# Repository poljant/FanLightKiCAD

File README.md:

# FanLightKiCAD
PCB FanLight
Płyta PCB do programu FanLight.
https://github.com/poljant/FanLight.git
W katalogu /GERBER/ pliki do wykonania PCB np. przez JLCPCB.

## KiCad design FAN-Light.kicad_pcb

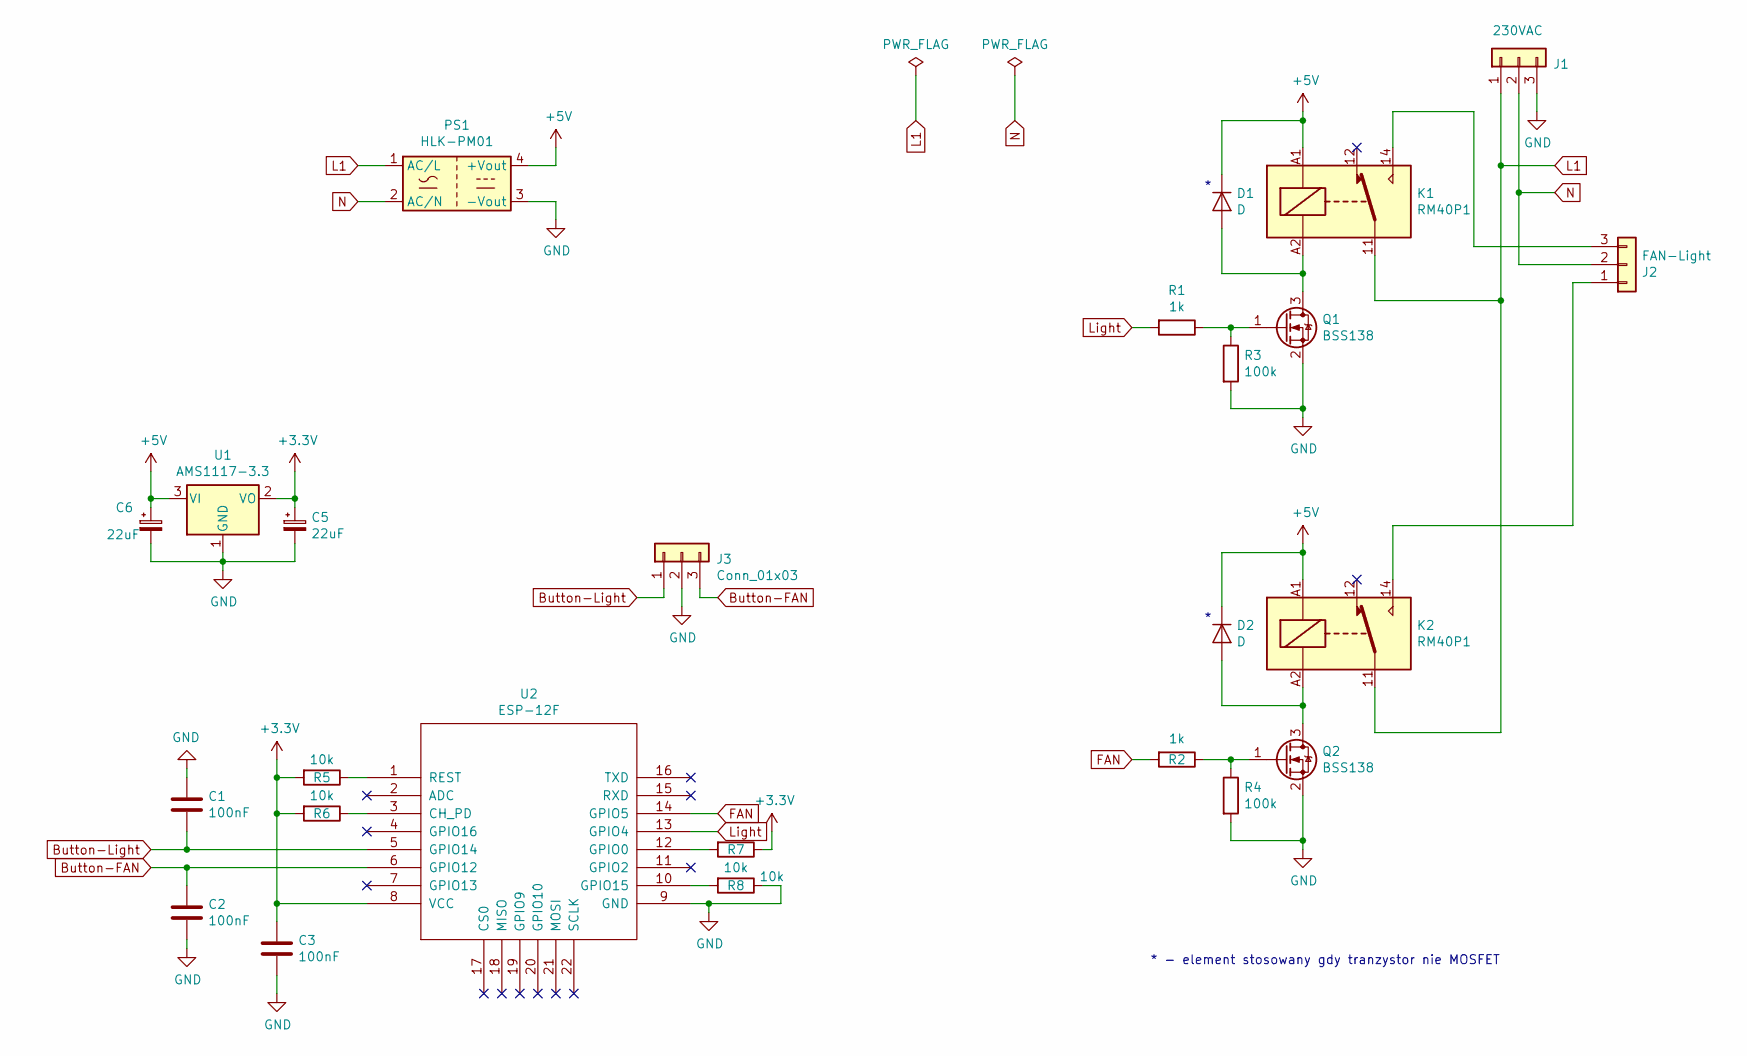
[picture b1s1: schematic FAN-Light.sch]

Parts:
C1, C2, C3: 100nF; R_1206_3216Metric_Pad1.42x1.75mm_HandSolder
C5, C6: 22uF; CP_Elec_4x5.7
D1, D2: D; D_1206_3216Metric_Pad1.42x1.75mm_HandSolder
J1: 230VAC; TerminalBlock_bornier-3_P5.08mm
J2: FAN-Light; TerminalBlock_bornier-3_P5.08mm
J3: Conn_01x03; PinHeader_1x03_P2.54mm_Vertical
K1, K2: RM40P1; Relay_Relpol-RM40-1P
PS1: HLK-PM01; CONV_HLK-5M05
Q1, Q2: BSS138; SOT-23
R1, R2: 1k; R_0805_2012Metric_Pad1.15x1.40mm_HandSolder
R3, R4: 100k; R_0805_2012Metric_Pad1.15x1.40mm_HandSolder
R5, R6, R7, R8: 10k; R_0805_2012Metric_Pad1.15x1.40mm_HandSolder
U1: AMS1117-3.3; SOT-223-3_TabPin2
U2: ESP-12F; ESP-12E_SMD

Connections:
+3V3: C3.1, C5.1, R5.2, R6.2, R7.1, U1.2 (VO), U2.8 (VCC)
+5V: C6.1, D1.1 (K), D2.1 (K), K1.A1, K2.A1, PS1.4 (+Vout), U1.3 (VI)
Button-FAN: C2.1, J3.3, U2.6 (GPIO12)
Button-Light: C1.2, J3.1, U2.5 (GPIO14)
FAN: R2.2, U2.14 (GPIO5)
GND: C1.1, C2.2, C3.2, C5.2, C6.2, J1.3, J3.2, PS1.3 (-Vout), Q1.2 (S), Q2.2 (S), R3.2, R4.2, R8.1, U1.1 (GND), U2.9 (GND)
L1: J1.1, K1.11, K2.11, PS1.1 (AC/L)
Light: R1.2, U2.13 (GPIO4)
N: J1.2, J2.2, PS1.2 (AC/N)
unnamed: D1.2 (A), K1.A2, Q1.3 (D)
unnamed: D2.2 (A), K2.A2, Q2.3 (D)
unnamed: J2.1, K2.14
unnamed: J2.3, K1.14
unnamed: Q1.1 (G), R1.1, R3.1
unnamed: Q2.1 (G), R2.1, R4.1
unnamed: R5.1, U2.1 (REST)
unnamed: R6.1, U2.3 (CH_PD)
unnamed: R7.2, U2.12 (GPIO0)
unnamed: R8.2, U2.10 (GPIO15)

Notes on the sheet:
* - element stosowany gdy tranzystor nie MOSFET

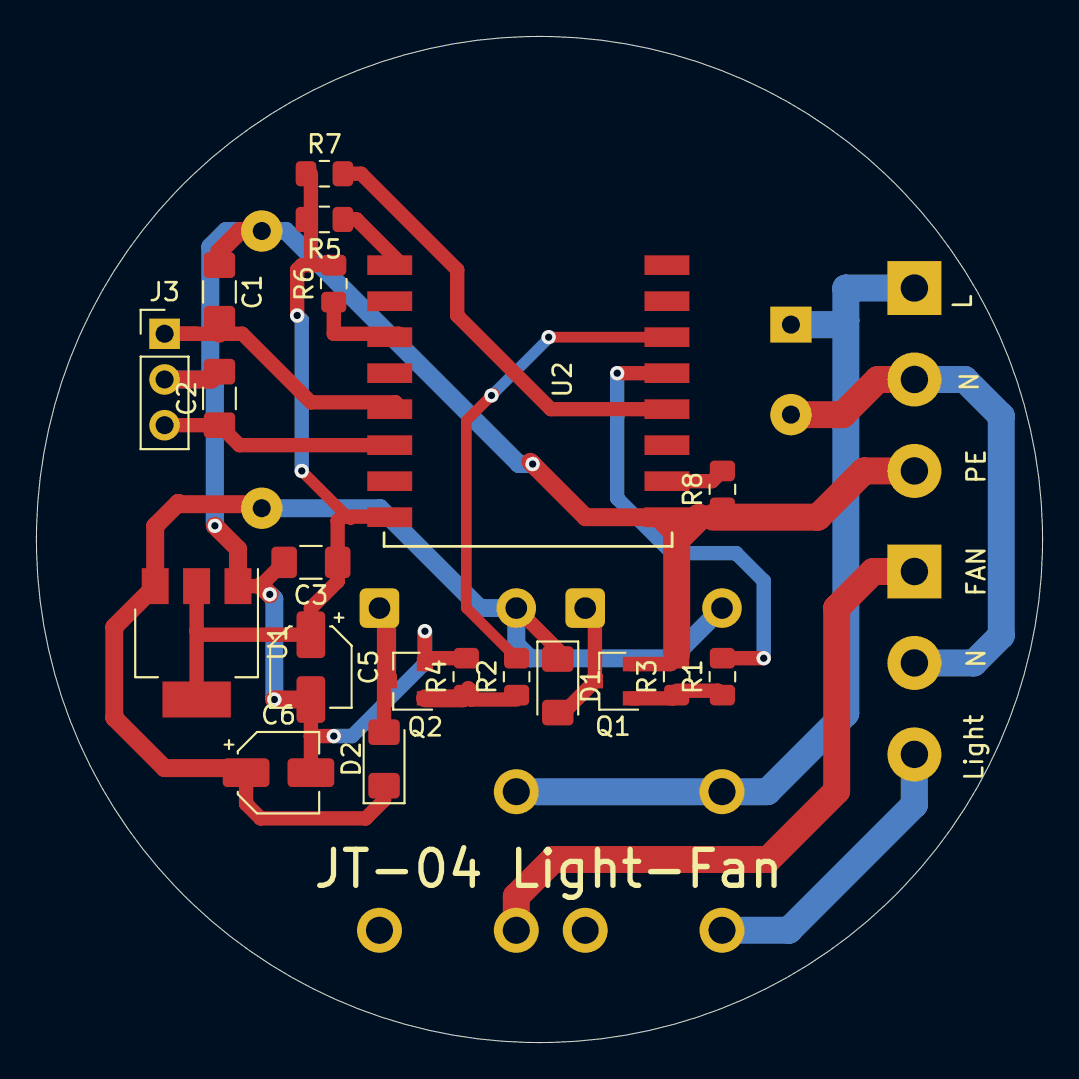
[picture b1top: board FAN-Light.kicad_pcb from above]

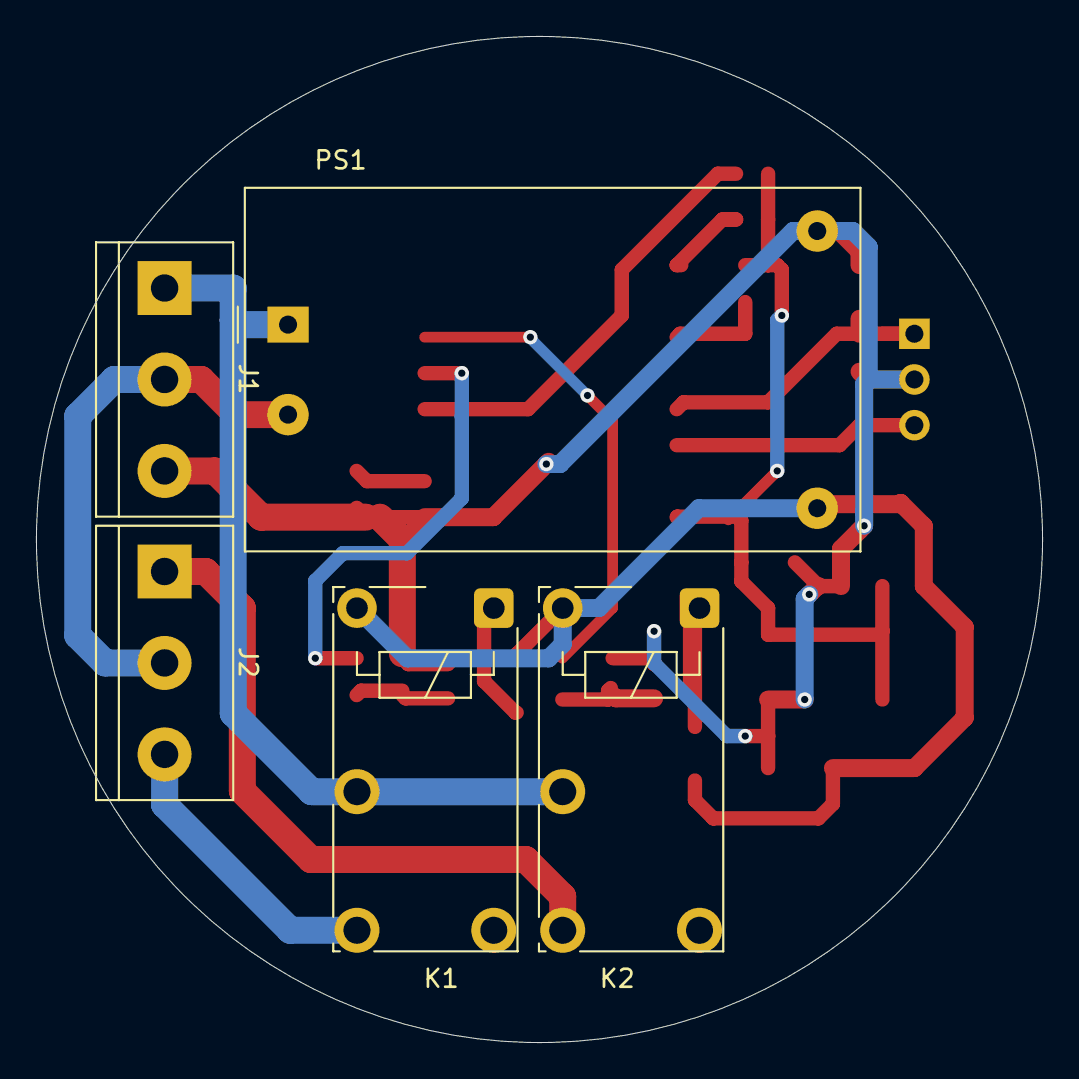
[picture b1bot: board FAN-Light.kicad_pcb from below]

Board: 2 copper layers, 55.9 x 55.9 mm, 25 parts (5 on the bottom side), 19 nets.

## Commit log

2021-11-22 dodanie plików
2021-11-22 dodano opis programu FanLight
